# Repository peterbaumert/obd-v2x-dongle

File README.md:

# obd-v2x-dongle

Hobby OBD-II plug-in dongle that reads vehicle data, receives ITS-G5 (802.11p) V2X messages and uploads everything over LTE.

> **Receive-only for ITS-G5.** Transmitting on the 5.9 GHz ITS band requires EN 302 571 compliant equipment (or an experimental licence from the Bundesnetzagentur). This project does not transmit V2X messages.

## Status

**Rev 2 is ordered** (2026-11-26, PCBWay, assembled; boards expected around the turn of the year). Nothing has been
built yet: rev 1 was cancelled before production in favour of rev 2, so the first rev 2 boards are also the first
test of the circuit and the firmware. Details: [`rev2/README.md`](rev2/README.md); order, parts and cost:
[`rev2/docs/bom-notes.md`](rev2/docs/bom-notes.md).

## Architecture

```
OBD-II J1962 plug
 ├─ pin 16 (+12 V) ──► reverse-polarity + TVS (ISO 7637 / 16750) ──► 3 A buck ──► 3.8 V (LTE)  ──► 3.3 V LDO (logic)
 ├─ pin 6/14 (CAN) ──► CAN transceiver ──► ESP32-C5 TWAI
 ├─ pin 7 (K-Line) ──► K-Line transceiver ──► ESP32-C5 UART
 └─ pin 4/5 (GND)

ESP32-C5-WROOM-1U ── u.FL ──► 5.9 GHz antenna   (ITS-G5 RX via esphome-its-g5, BLE for setup)
        │ UART
Quectel EC200U-EU (LTE Cat 1 + GNSS) ── LTE antenna (U.FL), GNSS patch with SAW + LNA front end, micro-SIM
1S LiPo backup cell with charger and power mux
```

### Power management
- Ignition detection (supply > ~13.2 V or CAN activity) to sleep the modem when parked
- Low-battery cutoff (~11.8 V) to avoid draining the car battery
- Cranking ride-through down to ~6 V

## Rev 2 (current)

Two stacked 45 × 45 mm boards (4 layers each, joined by 2 × 8 headers and two spacers) in a 3D-printed case of
**68.1 × 49.6 × 26.4 mm including the plug**. The carrier holds the plug, power and the LTE modem; the upper board the
ESP32-C5, the transceivers, the SIM, the charger and the GNSS patch.

| Carrier (plug, power, LTE modem underneath) | Upper board (ESP32-C5, transceivers, SIM, GNSS patch on top) |
|---|---|
|  |  |
|  |  |

Renders from KiCad (`rev2/hardware/tools/render.py`); the LTE modem and the GNSS patch have no 3D model, so only
their pads show.

## Repo layout

| Path | Contents |
|---|---|
| `rev2/` | Rev 2, ordered: `hardware/` (two KiCad 10 projects, the assembly panel, tools), `mechanical/` (stack model, case), `docs/` (BOMs, order notes) |
| `rev1/` | Rev 1, a single 52 × 64.4 mm board: fully designed and routed, cancelled before production. Kept as the reference circuit and for its bring-up procedure |
| `firmware/` | ESP32-C5 firmware (ESPHome), shared by both revisions |

## Related

- [esphome-its-g5](https://github.com/peterbaumert/esphome-its-g5) — ESP32-C5 ITS-G5 receiver component

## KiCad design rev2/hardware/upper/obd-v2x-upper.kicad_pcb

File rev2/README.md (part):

# Rev 2: two stacked boards in a 25 mm case

Status: **both boards placed and routed after a layout review (2026-11-21): nothing unconnected, no rule errors,
schematic parity 0; stack model and case check pass; case fit tests printed (2026-11-22).** Order files, stock
check and order notes are ready (2026-11-24, [`docs/bom-notes.md`](docs/bom-notes.md)). **Ordered from PCBWay on
2026-11-26** (one panel, 5 bare + 2 assembled, i.e. two dongles); PCBWay's engineering questions were answered on
2026-11-27 (mouse-bite spacing, and solder-mask openings on the through-hole pads that the panel file had lost, see
"Ordering"), so the boards are due around the turn of the year. The rev 1 order (`../rev1/`) was cancelled on
2026-11-24 in favour of rev 2, so the shared circuit has not been tested on a built board.
Rev 2 lives in this folder (`hardware/`, `mechanical/`, `docs/`). The firmware (`../firmware/`) is shared.

## Goal

Close to the size of a commercial OBD tracker (about 67 × 50 × 25 mm): **68.1 × 49.6 × 26.4 mm including the plug**, instead of rev 1's
87.4 × 56.6 × 34.1 mm. Same functions as rev 1 except for the changes under "Decisions".

## How it gets smaller

Rev 1 is one 52 × 64.4 mm board. The 18 mm above it (the height of the OBD plug) is mostly empty, and parts up to
10 mm tall hang below it. Rev 2 uses that space:

- **Same OBD plug** (CR-PG001, 90° through-hole), still entirely in front of the board edge.
- **Two boards of about 45 × 45 mm**, stacked, joined by board-to-board headers.
- **Carrier board** (lower): the plug, and the LTE module flat on the underside. Nothing else below the board is
  taller than the module (2.6 mm at most).
- **Upper board**: sits 12 mm above the carrier, inside the plug's own height.

### Height budget (z = 0 at the carrier's bottom face)

| From | To | What |
|---|---|---|
| −4.5 | −2.9 | floor, 1.6 mm |
| −2.9 | 0 | EC200U (2.4 ± 0.2 mm) + 0.3 mm clearance; the plug's leg tips reach −1.0 |
| 0 | 1.6 | carrier board |
| 1.6 | 13.6 | gap between the boards, 12.0 mm: carrier top-side parts, the backup cell, upper-board underside parts |
| 13.6 | 15.2 | upper board |
| 15.2 | 19.9 | GNSS patch (4.0 ± 0.4 mm) + clearance; the plug's key ends at 18.3 |
| 19.9 | 21.9 | roof, 2.0 mm, with a 1 mm pocket over the patch's feed-pin head |

Total **26.4 mm**.

- **The gap is 12.0 mm, set by M2.5 × 12 mm spacers** in the two front corners. The connectors must not bottom
  out first. A surface-mount header and socket stand on their leads and bottom out at 12.1 ± 0.4 mm, which would
  bow the boards. So the upper board carries a through-hole header (2.5 mm base, flat on the board) and the
  carrier a surface-mount socket (top 8.9 mm above its board): 11.4 mm, 11.8 at most, 0.6 mm short of bottoming.
  The header pins still reach 5.4 mm into the socket.
- **The plug sits as in rev 1**, 1.0 mm below the carrier's bottom face. Its legs end 1.0 mm under the upper
  board (drawing: upper leg row 13.2 mm above the housing bottom, legs 0.8 mm thick).

### Footprint

- Width: 45 mm board + 2 × 0.3 mm gap + 2 × 2 mm wall = **49.6 mm**.
- Length: 2 mm rear wall + 0.3 mm gap + 45 mm board + 0.35 mm + 20 mm plug = **67.7 mm**. The case front ends at the
  plug's retention groove, as in rev 1.

### Does it fit? (part areas from the rev 1 board)

One side of a 45 × 45 mm board is 2025 mm². Rev 1 uses 1272 mm² of parts on top and 1047 mm² below, on 3349 mm².

| Part | Size | Height | Goes on |
|---|---|---|---|
| EC200U-EU | 28 × 31 mm | 2.4 ± 0.2 mm | carrier, underside |
| ESP32-C5-WROOM-1U | 18 × 21 mm | 3.4 mm | upper board, underside |
| Micro-SIM holder | about 16 × 15 mm | 1.45 mm | upper board, underside, at the left edge (slot in the case) |
| Buck inductor | 7 × 7 mm | 4.8 mm | carrier, top side |
| 220 µF tantalums | 7 × 4 mm | 3.1 mm | carrier, top side |
| USB-C | 9 × 8 mm | 3.3 mm | upper board, rear edge |
| Plug legs | 32 × 7 mm | through-hole | carrier, front edge, blocks both sides |

## Board split

Decided by area: with everything except the ESP32 on the carrier, its free area would be about 65 % full and the
upper board's about 9 %. With the split below it is about 45 % and 26 % (courtyard areas from the rev 1 board).

**Carrier:** J201 with the bus protection at its pins (CAN TVS, K-line capacitor and TVS), input protection, buck,
3.3 V regulator, EC200U with its supply caps, level shifter, LTE U.FL, GNSS U.FL (jumper to the upper board), the
cell connector and the power mux. The mux and the cell connector sit here because the modem's supply current then
never has to cross the connectors. 73 parts.

**Upper board:** ESP32-C5 module, USB-C, LED, RESET / BOOT buttons, the CAN and K-line transceivers, the micro-SIM
holder with its resistors and capacitors, the cell charger with its NTC (only 70 mA of charge current crosses the
stack; the NTC sits over the cell), the VIN sense divider, the open-collector drivers for the modem's PWRKEY and
RESET_N, and the ceramic GNSS patch on the top side with its front end and a U.FL for the jumper. 65 parts.

The carrier is the crowded one (the modem takes most of its underside, the cell limits part height over half of
its top), so everything that does not have to be next to the plug, the modem or the supply path is upstairs.

**Across the connectors** (two 2 × 8, 32 pins): 18 lines, 3 × 3.3 V, 1 × VSYS 3.8 V and 10 × GND.

| Connector | Lines |
|---|---|
| left (J601 / J701): the plug's bus pins and the modem's UART side | CANH, CANL (a facing pin pair), K_LINE, VIN_PROT (vehicle voltage for the K-line pull-up), modem UART TX / RX / RTS / CTS, STATUS |
| right (J602 / J702): the modem's SIM and power-key side | PWRKEY and RESET_N (open-collector lines), LTE power enable, USB VBUS, SIM VDD / RST / CLK / DATA, VSYS 3.8 V, VCELL (charger to cell) |

The pin lists are `STACK_A` / `STACK_B` in `hardware/tools/gen_schematic.py`.

## Schematics

Two KiCad 10 projects, generated like rev 1's (edit `hardware/tools/gen_schematic.py`, then run it):

| Project | Sheets |
|---|---|
| `hardware/carrier/obd-v2x-carrier` | power, vehicle, lte, battery (cell connector, power mux), stack_carrier |
| `hardware/upper/obd-v2x-upper` | mcu, xcvr (transceivers), sim, gnss, charger, sense, keys, stack_upper |

```bash
python rev2/hardware/tools/gen_schematic.py     # writes both projects
python rev2/hardware/tools/check_stack.py       # same net on mating connector pins, nothing shared left uncrossed
python rev2/hardware/tools/check_vs_rev1.py     # both boards joined = rev 1's circuit, apart from the listed changes
kicad-cli sch erc rev2/hardware/carrier/obd-v2x-carrier.kicad_sch
kicad-cli sch erc rev2/hardware/upper/obd-v2x-upper.kicad_sch
```

State: ERC 0 violations on both boards, `check_stack.py` passes (21 nets cross), and `check_vs_rev1.py` confirms
that the two boards joined through the connectors are connected exactly like rev 1's reviewed netlist, apart from
the intended changes. The circuits are rev 1's with
these changes: eSIM and SIM switch removed (IO12 is a spare test pad), micro-SIM holder, side-entry battery
connector, the two board-to-board connectors with spacer holes, and the GNSS patch with its front end.

GNSS on the upper board (sheet `gnss`): patch -> SKY65943-11 -> 33 pF DC block -> U.FL J801, joined by a jumper
cable to the carrier's GNSS socket J403. The front end is powered on the upper board, from the MCU pin that
switches the modem on (LTE_PWR_EN, 3 mA) through 100 Ω and 100 nF: about 3.0 V, under the part's 3.3 V limit, and
only while the modem is on. Its enable pin is tied to that supply. So the coax carries no DC and rev 1's antenna
bias switch (U405 with L401, C418, C419, C420, R415) is gone. R802 (not fitted) is a bypass link for trying the
bare patch.

New footprints, each drawn from the manufacturer's drawing (sources in `hardware/lib/gen_footprints.py`):
Molex 78646-3001 micro-SIM holder, Skyworks SKY65943-11, Taoglas CGGBP.25.4.A.02 patch.

Not done yet:

- **Footprint review against real parts:** the three new footprints come from the drawings and have not been
  checked on paper prints or parts (PCBWay's review saw them before assembly). The SKY65943-11's ground pad sizes
  and the patch's feed pad (1.4 mm on top, 2.2 mm on the bottom) are my choices.
- **GNSS details to confirm:** whether the SKY65943-11's RF pins carry DC (the data sheet does not say; a DC
  block sits on its output for that reason), and ESD protection at the patch (the part is rated only 250 V HBM).

## Boards

`<KiCad>/bin/python rev2/hardware/tools/gen_pcb.py carrier|upper` builds each board from its schematic: 45 × 45 mm
outline, rules, all footprints with their nets, ground pours. `--force` regenerates a board and loses any routing.

| Board | Layers | Why |
|---|---|---|
| carrier | 4 | The modem has pads under its body and the LTE antenna line needs a ground layer right below it |
| upper | 4 | F.Cu under the GNSS patch has to stay solid ground (the patch's ground plane); with that, two layers left no room for the SIM lines and the rest. In1 GND plane, In2 routing |

No paid impedance control: the antenna lines are designed to the fab's standard stack-up. ENIG on both boards (they
are ordered as one panel; flat pads for the modem and the QFNs).

Placement:

- **The parts that define the stack are placed as in the stack model:** plug, connectors, spacer holes, modem,
  ESP32 module, USB-C, micro-SIM holder, GNSS patch and front end, and the carrier's tall parts (battery connector,
  inductor, tantalums) in its front half.
- **Every other part is placed automatically** next to a part it shares a net with, and only where it fits by
  height: at most 2.9 mm under the cell, 2.65 mm on the carrier's underside, 0.7 mm on the upper board's underside
  over the plug legs. The heights are a table in `gen_pcb.py` (by footprint): data-sheet maxima for the tall parts,
  typical values for the rest. That was the starting point; the layout review and routing below moved many parts
  by hand.
- **Antenna sockets:** LTE and GNSS U.FL in the carrier's rear right corner, beside the cell.
- **The lid side of the upper board carries what must be reached or seen:** the two buttons and the LED.
  The case lid has pin holes and a 3 mm hole for a light rod there.
- **Changes the placement forced:** the connectors sit 0.6 mm inside the board edges (their SMD pads need 8.2 mm);
  the buck regulator uses the footprint without thermal vias, because the modem's pads are on the other side; the
  input TVS is on the carrier's underside beside the modem; the patch sits 1.5 mm left of centre so the USB-C
  socket's legs are not under it.

- **Modem orientation:** antenna pins at the rear, next to the LTE and GNSS sockets in the rear corners; UART,
  status and supply pins on its left side, where a strip of the underside stays free (level shifter, input TVS);
  SIM and power-key pins at the front and right. The connector pins are assigned to match.

### Routing

```bash
FREEROUTING_JAR=<freerouting-2.x.jar> <KiCad>/bin/python rev2/hardware/tools/autoroute.py upper   # Freerouting, Java 25
<KiCad>/bin/python rev2/hardware/tools/stitch.py upper        # GND vias where the two pours overlap
<KiCad>/bin/python rev2/hardware/tools/route_unconnected.py carrier|upper   # single connections with maze.py
```

- **Both boards are routed.** DRC on each: 0 unconnected, schematic parity 0, no rule errors. What remains is
  part outlines from the libraries touching neighbouring pads (the fab clips silkscreen off pads) and the USB-C outline
  at the rear edge, which the connector overhangs on purpose.
- **Upper board:** placed, then routed from scratch on 4 layers with `autoroute.py`; `finish.py`, `stitch.py`,
  `islands.py`, `padvia.py`; a few connections by hand. No signal copper on F.Cu under the patch.
- **Carrier:** the buck and the modem supply were re-placed at their pins (see "Layout review"), the nets around
  them ripped up and routed again with Freerouting (the rest locked), the last connections by hand in KiCad / the
  KiCad MCP: VBUCK into the power mux over In2, the compensation / feedback column re-ordered (COMP on F.Cu beside it,
  FB over In2, their ground to U102's exposed pad), the UART lines and K-line re-routed around them.
- **From here on the two `.kicad_pcb` files are the source.** `gen_pcb.py --force` rebuilds the placement but
  loses the routing and the hand edits; `PLACE` in `gen_pcb.py` records the positions of the parts it lists.
- **Rules:** Switch class (buck switch node) 0.8 mm, Modem class (VBAT_LTE) 0.6 mm, other supplies 0.4 mm on the
  carrier; vehicle-voltage nets keep 0.2 mm clearance; one thermal-relief spoke is enough. `widen.py` then widened
  every supply segment that had room: the switch node is 10 mm of 0.8-1.0 mm track on F.Cu without vias, VBAT_LTE
  mostly 1.0 mm. RF lines are 0.32 mm throughout (0.27 mm only into the front end's own pads); the LTE line runs
  27 mm from the corner U.FL (about 0.2-0.3 dB).
- **Under the carrier's top parts is the modem:** its edge pads (2.5 mm long, 0.5 mm apart) leave no room for a via
  beside them, and its centre GND pads only leave a few gaps. Check the underside before placing a via there.
- **Checked 2026-11-21:** buck loop by eye (C102 over VIN, D103's cathode under SW, L101 beside U102), switch node,
  supply widths, RF widths. Silkscreen: references placed beside their parts; about 30 per board have no free spot
  and are hidden (the CPL file carries the positions). Not checkable here: the patch on the 45 mm board (measure).

| Carrier, top | Carrier, underside | Upper, top | Upper, underside |
|---|---|---|---|
|  |  |  |  |

| Tool | What it does |
|---|---|
| `autoroute.py` | Freerouting on a DSN export (carrier: In1 declared a GND plane) |
| `route_unconnected.py`, `maze.py` | single connections, from rev 1 |
| `repair.py` | fixes via drills and thin tracks; rips up and re-routes every signal net in a rule error |
| `finish.py` | routes what is still open, GND pads included, with narrower tracks |
| `stitch.py` | GND vias where the pours of all layers overlap |
| `islands.py` | a via for each pour fragment that has none |
| `movepart.py` | moves a two-pad part next to the pin it belongs to and reconnects it |
| `localfix.py` | blunt local rip-up around a blocked pin; made things worse when tried, kept for reference |
| `padvia.py` | a GND via for a floating GND pad (rips signal nets in the way; run `finish.py` after) |
| `swapfp.py` | replaces placed footprints with the library version, or with another footprint (`REF=Lib:Name`) |
| `silk.py` | puts each reference beside its part where it is clear of pads and other silkscreen, or hides it |
| `widen.py` | widens supply tracks (and necked-down RF lines back to 0.32 mm) wherever the clearance allows |
| `fab.py` | order files per board: Gerber zip, assembly BOM, pick-and-place file; full BOMs to `docs/` |
| `check_stock.py` | LCSC stock of every part with an MPN, from the BOMs that `fab.py` writes |
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
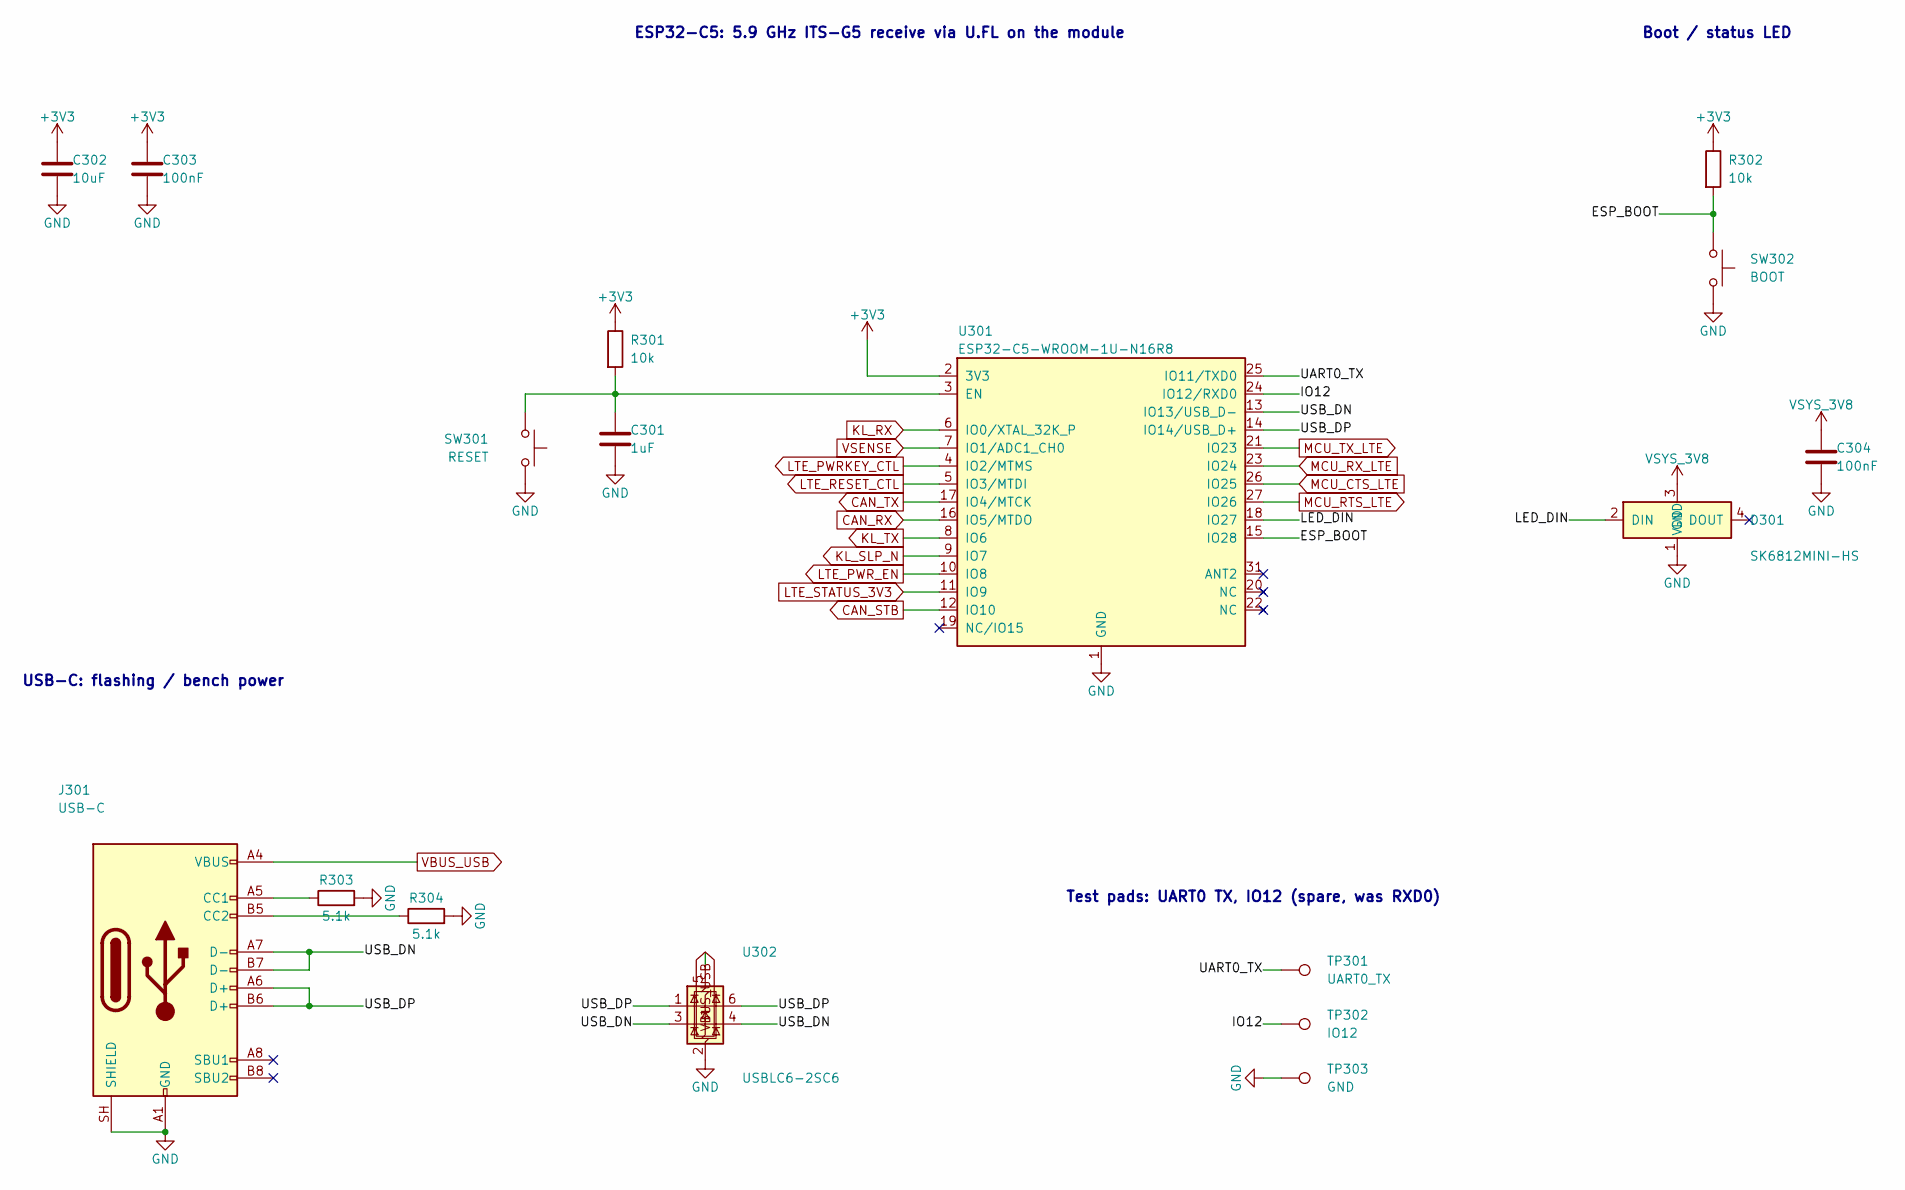
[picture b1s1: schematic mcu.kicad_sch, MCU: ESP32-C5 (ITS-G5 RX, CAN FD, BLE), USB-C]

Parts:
C301: 1uF; C_0603_1608Metric
C302: 10uF; C_0805_2012Metric
C303, C304: 100nF; C_0603_1608Metric
D301: SK6812MINI-HS; LED_SK6812MINI-HS_3.7x3.5mm; MPN SK6812MINI-HS; LCSC C2922787
J301: USB-C; USB_C_Receptacle_HRO_TYPE-C-31-M-12; MPN TYPE-C-31-M-12; LCSC C165948
R301, R302: 10k; R_0603_1608Metric
R303, R304: 5.1k; R_0603_1608Metric
SW301: RESET; SW_SPST_TL3342; MPN TL3342F450QG; LCSC C2886897
SW302: BOOT; SW_SPST_TL3342; MPN TL3342F450QG; LCSC C2886897
TP301: UART0_TX; TestPoint_Pad_D1.0mm
TP302: IO12; TestPoint_Pad_D1.0mm
TP303: GND; TestPoint_Pad_D1.0mm
U301: ESP32-C5-WROOM-1U-N16R8; ESP32-C5-WROOM-1U; MPN ESP32-C5-WROOM-1U-N16R8-V1.2; LCSC C54951857
U302: USBLC6-2SC6; SOT-23-6; MPN USBLC6-2SC6; LCSC C2827654

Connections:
/MCU (ESP32-C5, USB)/ESP_BOOT: R302.2, SW302.1, U301.15 (IO28)
/MCU (ESP32-C5, USB)/IO12: TP302.1, U301.24 (IO12/RXD0)
/MCU (ESP32-C5, USB)/LED_DIN: D301.2 (DIN), U301.18 (IO27)
/MCU (ESP32-C5, USB)/UART0_TX: TP301.1, U301.25 (IO11/TXD0)
/MCU (ESP32-C5, USB)/USB_DN: J301.A7 (D-), J301.B7 (D-), U301.13 (IO13/USB_D-), U302.3 (I/O2), U302.4 (I/O2)
/MCU (ESP32-C5, USB)/USB_DP: J301.A6 (D+), J301.B6 (D+), U301.14 (IO14/USB_D+), U302.1 (I/O1), U302.6 (I/O1)
CAN_RX: U301.16 (IO5/MTDO); also elsewhere on the board
CAN_STB: U301.12 (IO10); also elsewhere on the board
CAN_TX: U301.17 (IO4/MTCK); also elsewhere on the board
KL_RX: U301.6 (IO0/XTAL_32K_P); also elsewhere on the board
KL_SLP_N: U301.9 (IO7); also elsewhere on the board
KL_TX: U301.8 (IO6); also elsewhere on the board
LTE_PWRKEY_CTL: U301.4 (IO2/MTMS); also elsewhere on the board
LTE_PWR_EN: U301.10 (IO8); also elsewhere on the board
LTE_RESET_CTL: U301.5 (IO3/MTDI); also elsewhere on the board
LTE_STATUS_3V3: U301.11 (IO9); also elsewhere on the board
MCU_CTS_LTE: U301.26 (IO25); also elsewhere on the board
MCU_RTS_LTE: U301.27 (IO26); also elsewhere on the board
MCU_RX_LTE: U301.23 (IO24); also elsewhere on the board
MCU_TX_LTE: U301.21 (IO23); also elsewhere on the board
unnamed: J301.A5 (CC1), R303.1
unnamed: J301.B5 (CC2), R304.1
unnamed: C301.1, R301.2, SW301.1, U301.3 (EN)
VBUS_USB: J301.A4 (VBUS), J301.A9 (VBUS), J301.B4 (VBUS), J301.B9 (VBUS), U302.5 (VBUS); also elsewhere on the board
VSENSE: U301.7 (IO1/ADC1_CH0); also elsewhere on the board

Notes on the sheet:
Test pads: UART0 TX, IO12 (spare, was RXD0)
USB-C: flashing / bench power
ESP32-C5: 5.9 GHz ITS-G5 receive via U.FL on the module
Boot / status LED

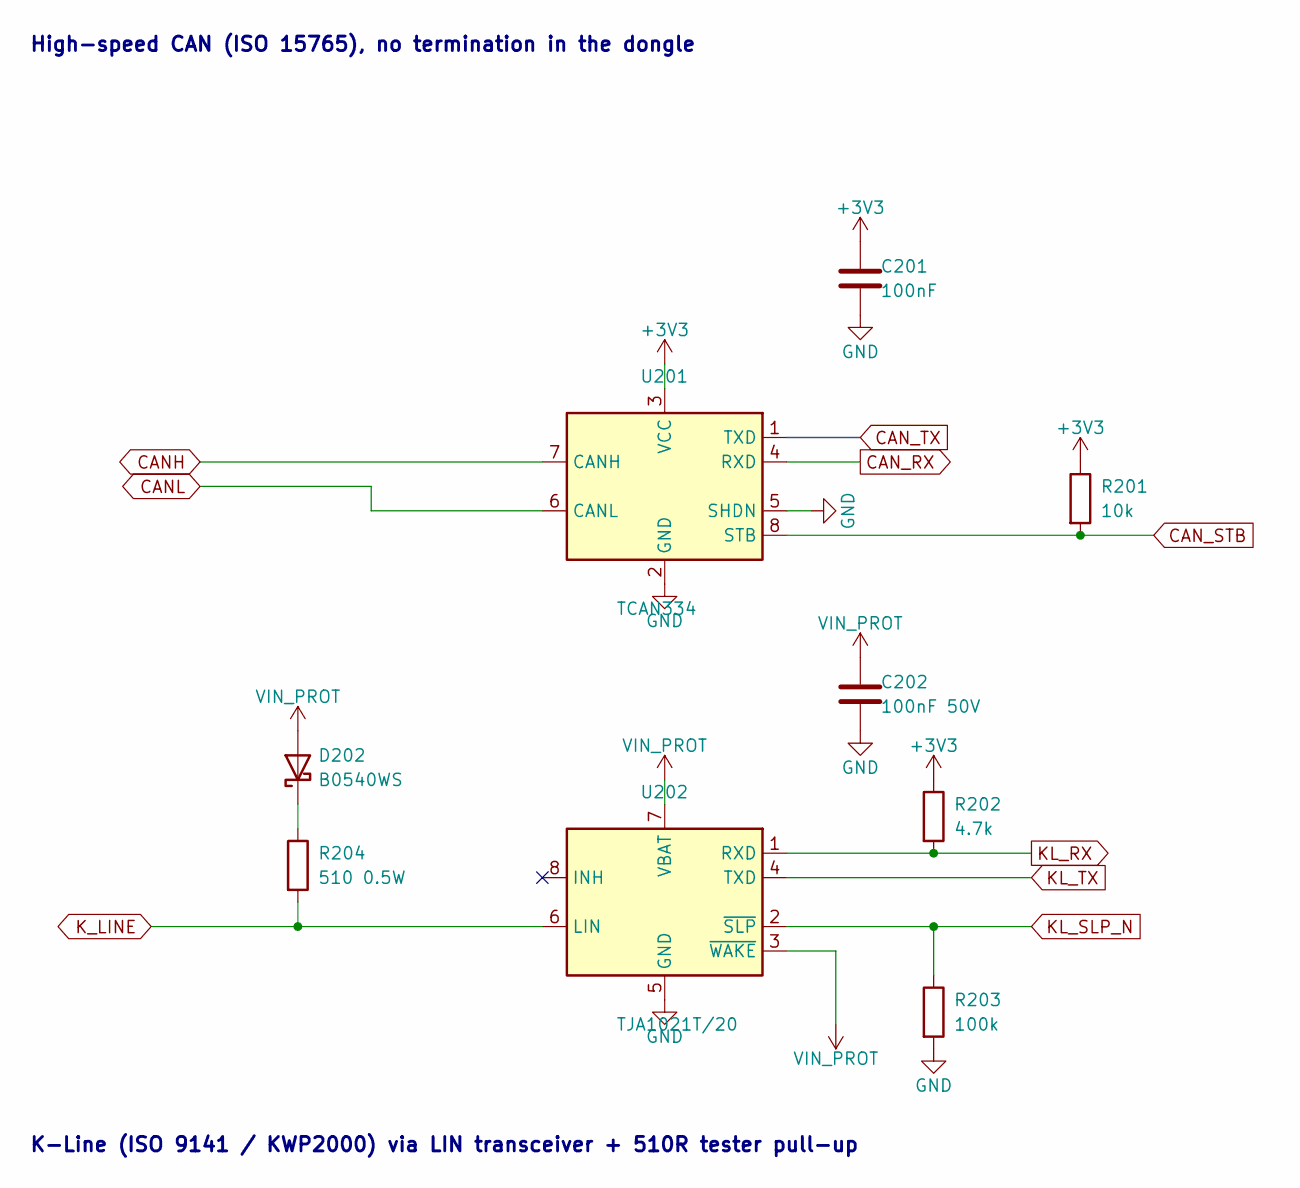
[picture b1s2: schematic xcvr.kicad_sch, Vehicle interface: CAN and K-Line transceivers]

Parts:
C201: 100nF; C_0603_1608Metric
C202: 100nF 50V; C_0603_1608Metric
D202: B0540WS; D_SOD-323; MPN B0540WS-7; LCSC C52754523
R201: 10k; R_0603_1608Metric
R202: 4.7k; R_0603_1608Metric
R203: 100k; R_0603_1608Metric
R204: 510 0.5W; R_1206_3216Metric
U201: TCAN334; SOIC-8_3.9x4.9mm_P1.27mm; MPN TCAN334DR; LCSC C2871143
U202: TJA1021T/20; SOIC-8_3.9x4.9mm_P1.27mm; MPN TJA1021T/20/CM,118; LCSC C128810

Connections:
CANH: U201.7 (CANH); also elsewhere on the board
CANL: U201.6 (CANL); also elsewhere on the board
CAN_RX: U201.4 (RXD); also elsewhere on the board
CAN_STB: R201.2, U201.8 (STB); also elsewhere on the board
CAN_TX: U201.1 (TXD); also elsewhere on the board
KL_RX: R202.2, U202.1 (RXD); also elsewhere on the board
KL_SLP_N: R203.1, U202.2 (~SLP); also elsewhere on the board
KL_TX: U202.4 (TXD); also elsewhere on the board
K_LINE: R204.2, U202.6 (LIN); also elsewhere on the board
unnamed: D202.1 (K), R204.1

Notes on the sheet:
High-speed CAN (ISO 15765), no termination in the dongle
K-Line (ISO 9141 / KWP2000) via LIN transceiver + 510R tester pull-up

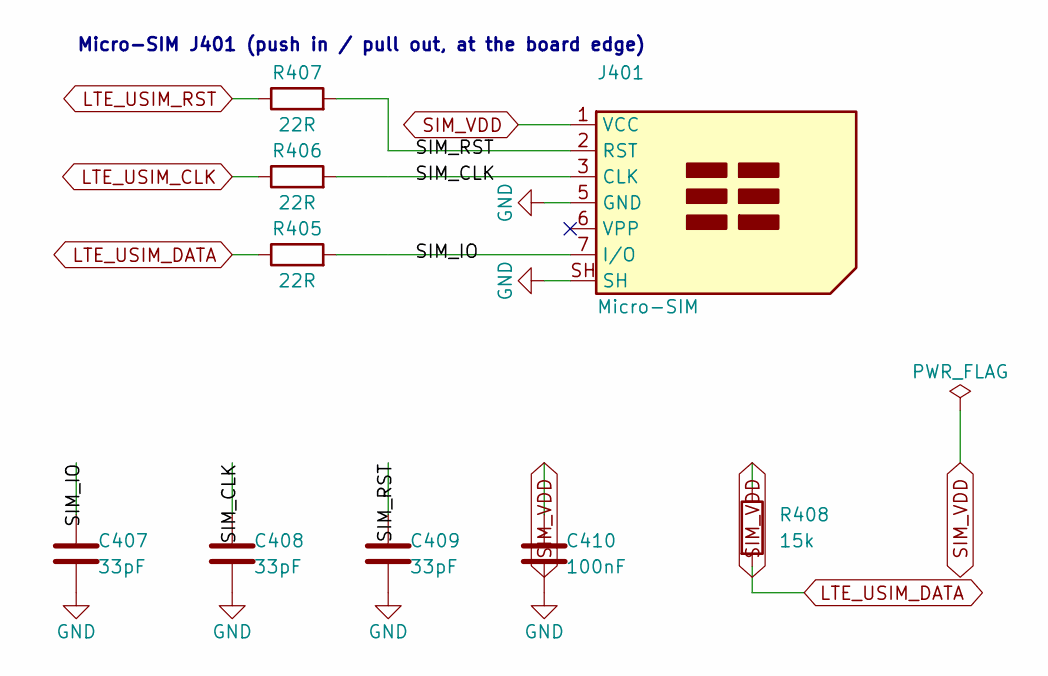
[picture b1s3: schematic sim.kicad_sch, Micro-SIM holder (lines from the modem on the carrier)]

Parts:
C407, C408, C409: 33pF; C_0402_1005Metric
C410: 100nF; C_0402_1005Metric
J401: Micro-SIM; microSIM_Molex_78646-3001; MPN 0786463001
R405, R406, R407: 22R; R_0402_1005Metric
R408: 15k; R_0402_1005Metric

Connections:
/Micro-SIM/SIM_CLK: C408.1, J401.3 (CLK), R406.2
/Micro-SIM/SIM_IO: C407.1, J401.7 (I/O), R405.2
/Micro-SIM/SIM_RST: C409.1, J401.2 (RST), R407.2
LTE_USIM_CLK: R406.1; also elsewhere on the board
LTE_USIM_DATA: R405.1, R408.2; also elsewhere on the board
LTE_USIM_RST: R407.1; also elsewhere on the board
SIM_VDD: C410.1, J401.1 (VCC), R408.1; also elsewhere on the board

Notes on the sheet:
Micro-SIM J401 (push in / pull out, at the board edge)

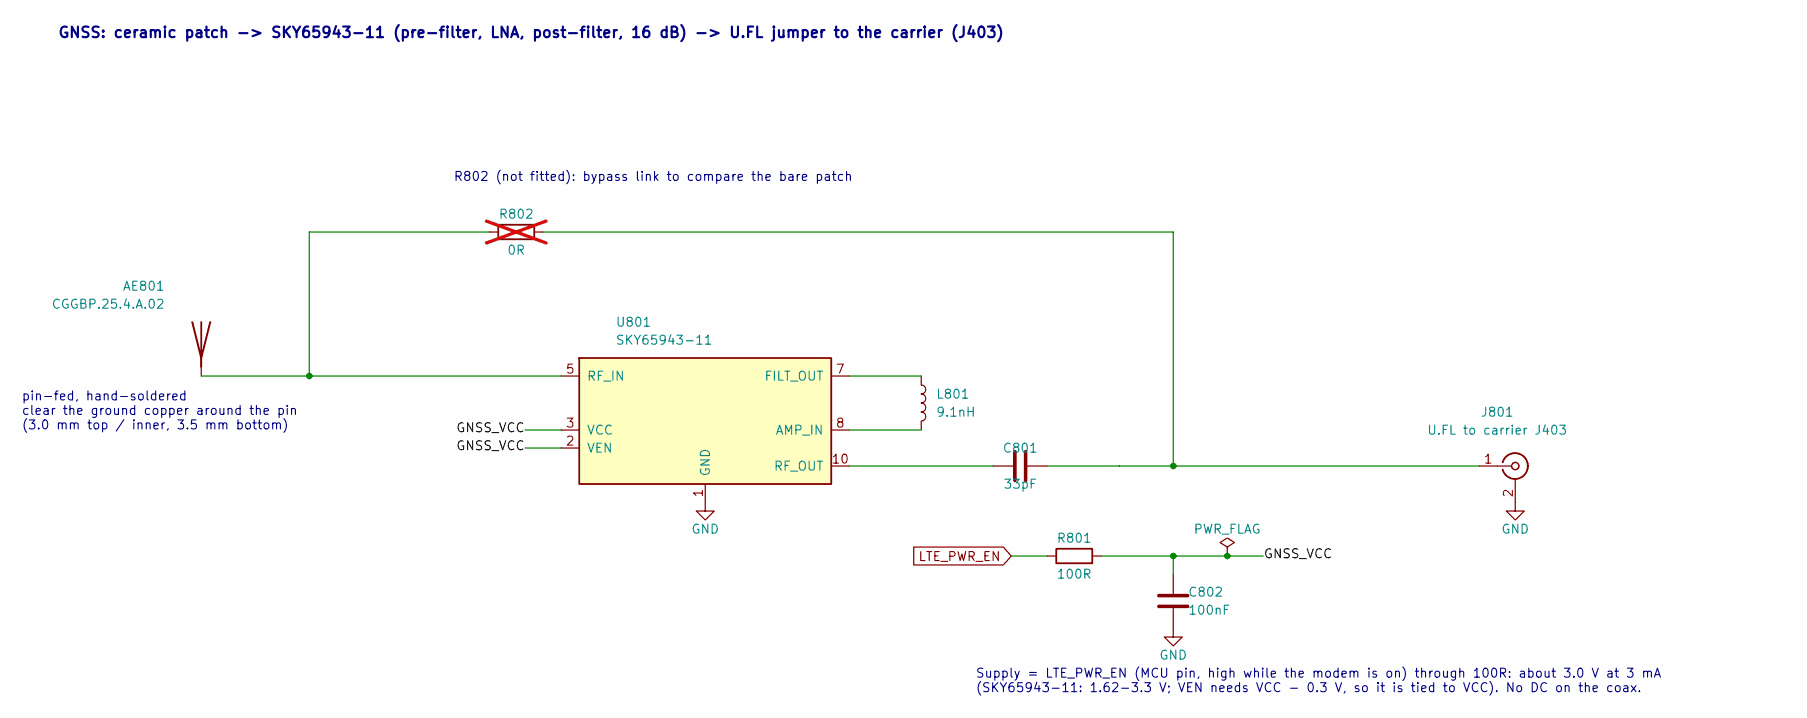
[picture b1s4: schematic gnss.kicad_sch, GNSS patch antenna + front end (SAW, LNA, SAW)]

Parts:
AE801: CGGBP.25.4.A.02; Antenna_Taoglas_CGGBP.25.4.A.02; MPN CGGBP.25.4.A.02
C801: 33pF; C_0402_1005Metric; MPN 0402CG330J500NT; LCSC C1562
C802: 100nF; C_0402_1005Metric
J801: U.FL to carrier J403; U.FL_Hirose_U.FL-R-SMT-1_Vertical; MPN U.FL-R-SMT-1(10); LCSC C88373
L801: 9.1nH; L_0402_1005Metric; MPN LQW15AN9N1J00D; LCSC C437364
R801: 100R; R_0402_1005Metric
R802: 0R; R_0402_1005Metric; not fitted
U801: SKY65943-11; Skyworks_SKY65943-11_MCM-10_2.5x2.5mm; MPN SKY65943-11; LCSC C2654442

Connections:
/GNSS patch + front end/GNSS_VCC: C802.1, R801.2, U801.2 (VEN), U801.3 (VCC)
LTE_PWR_EN: R801.1; also elsewhere on the board
unnamed: AE801.1, R802.1, U801.5 (RF_IN)
unnamed: C801.2, J801.1 (In), R802.2
unnamed: L801.2, U801.8 (AMP_IN)
unnamed: L801.1, U801.7 (FILT_OUT)
unnamed: C801.1, U801.10 (RF_OUT)

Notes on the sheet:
R802 (not fitted): bypass link to compare the bare patch
GNSS: ceramic patch -> SKY65943-11 (pre-filter, LNA, post-filter, 16 dB) -> U.FL jumper to the carrier (J403)
Supply = LTE_PWR_EN (MCU pin, high while the modem is on) through 100R: about 3.0 V at 3 mA (SKY65943-11: 1.62-3.3 V; VEN needs VCC - 0.3 V, so it is tied to VCC). No DC on the coax.
pin-fed, hand-soldered clear the ground copper around the pin (3.0 mm top / inner, 3.5 mm bottom)

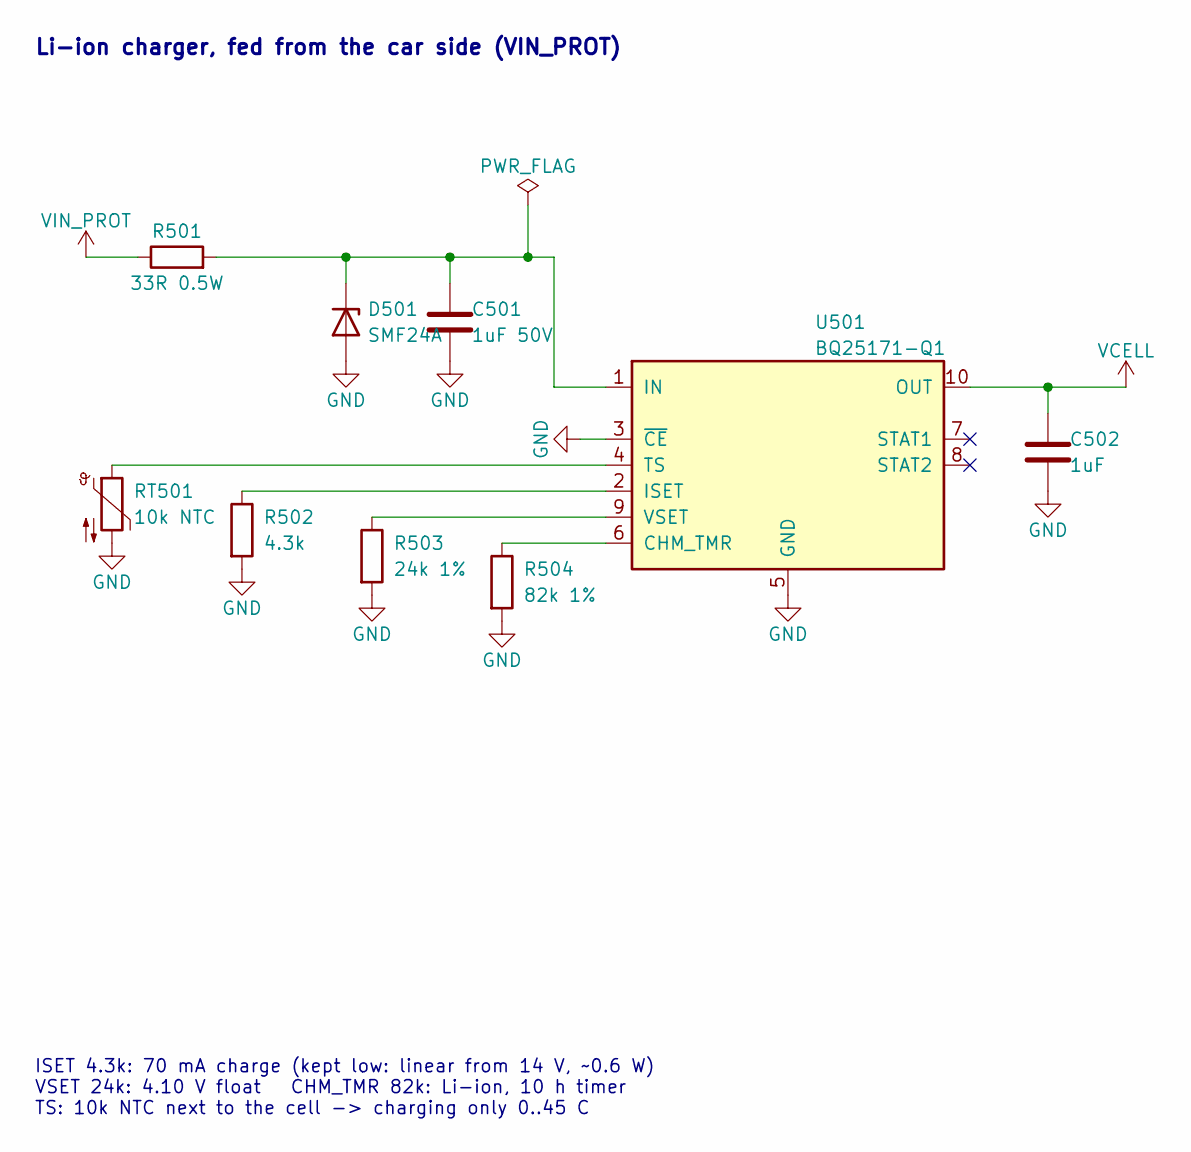
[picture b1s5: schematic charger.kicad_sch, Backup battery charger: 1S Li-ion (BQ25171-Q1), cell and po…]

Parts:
C501: 1uF 50V; C_0805_2012Metric
C502: 1uF; C_0603_1608Metric
D501: SMF24A; D_SOD-123F; MPN SMF24A; LCSC C315999
R501: 33R 0.5W; R_1206_3216Metric
R502: 4.3k; R_0603_1608Metric
R503: 24k 1%; R_0603_1608Metric
R504: 82k 1%; R_0603_1608Metric
RT501: 10k NTC; R_0603_1608Metric; MPN SDNT1608X103F3435FTF; LCSC C525660
U501: BQ25171-Q1; Texas_DRC0010J; MPN BQ25171QWDRCRQ1; LCSC C2861221

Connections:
unnamed: C501.1, D501.1 (K), R501.2, U501.1 (IN)
unnamed: R504.1, U501.6 (CHM_TMR)
unnamed: R502.1, U501.2 (ISET)
unnamed: RT501.1, U501.4 (TS)
unnamed: R503.1, U501.9 (VSET)
VCELL: C502.1, U501.10 (OUT); also elsewhere on the board

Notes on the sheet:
ISET 4.3k: 70 mA charge (kept low: linear from 14 V, ~0.6 W) VSET 24k: 4.10 V float CHM_TMR 82k: Li-ion, 10 h timer TS: 10k NTC next to the cell -> charging only 0..45 C
Li-ion charger, fed from the car side (VIN_PROT)

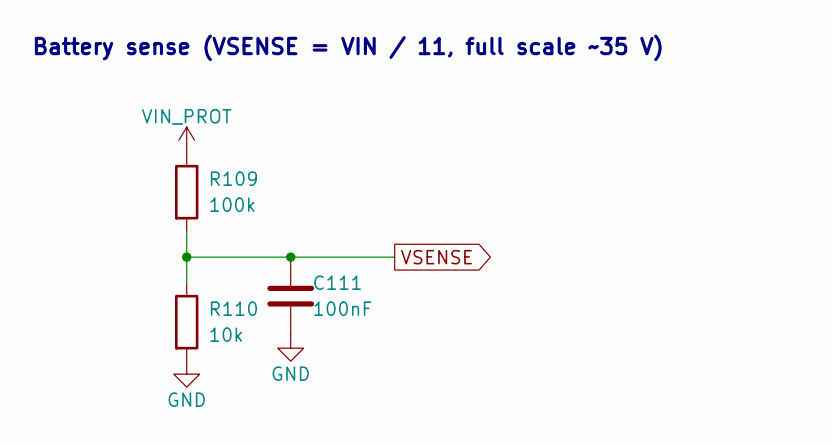
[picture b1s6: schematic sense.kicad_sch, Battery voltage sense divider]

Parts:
C111: 100nF; C_0603_1608Metric
R109: 100k; R_0603_1608Metric
R110: 10k; R_0603_1608Metric

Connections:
VSENSE: C111.1, R109.2, R110.1; also elsewhere on the board

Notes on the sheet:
Battery sense (VSENSE = VIN / 11, full scale ~35 V)

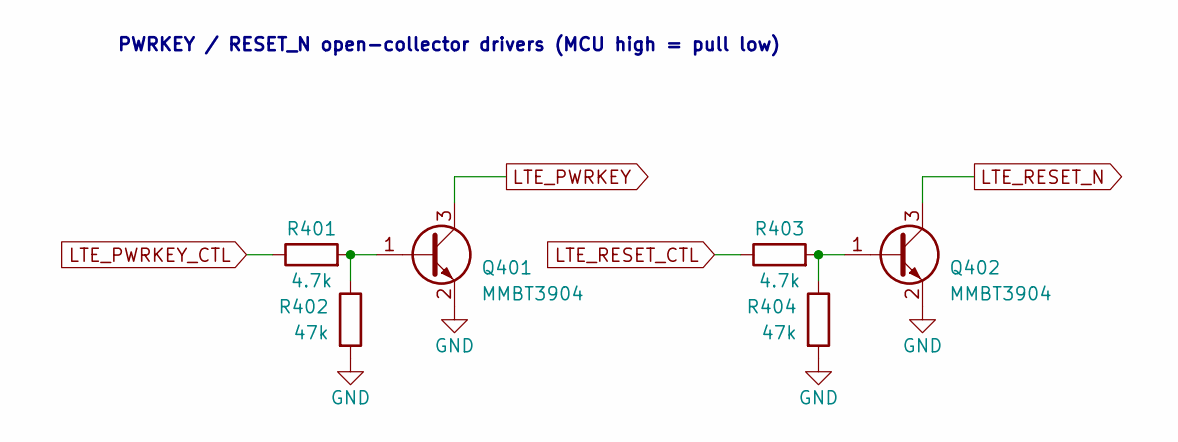
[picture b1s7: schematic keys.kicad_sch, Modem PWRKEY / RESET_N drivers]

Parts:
Q401, Q402: MMBT3904; SOT-23; MPN MMBT3904; LCSC C20526
R401, R403: 4.7k; R_0603_1608Metric
R402, R404: 47k; R_0603_1608Metric

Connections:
LTE_PWRKEY: Q401.3 (C); also elsewhere on the board
LTE_PWRKEY_CTL: R401.1; also elsewhere on the board
LTE_RESET_CTL: R403.1; also elsewhere on the board
LTE_RESET_N: Q402.3 (C); also elsewhere on the board
unnamed: Q401.1 (B), R401.2, R402.1
unnamed: Q402.1 (B), R403.2, R404.1

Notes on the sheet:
PWRKEY / RESET_N open-collector drivers (MCU high = pull low)

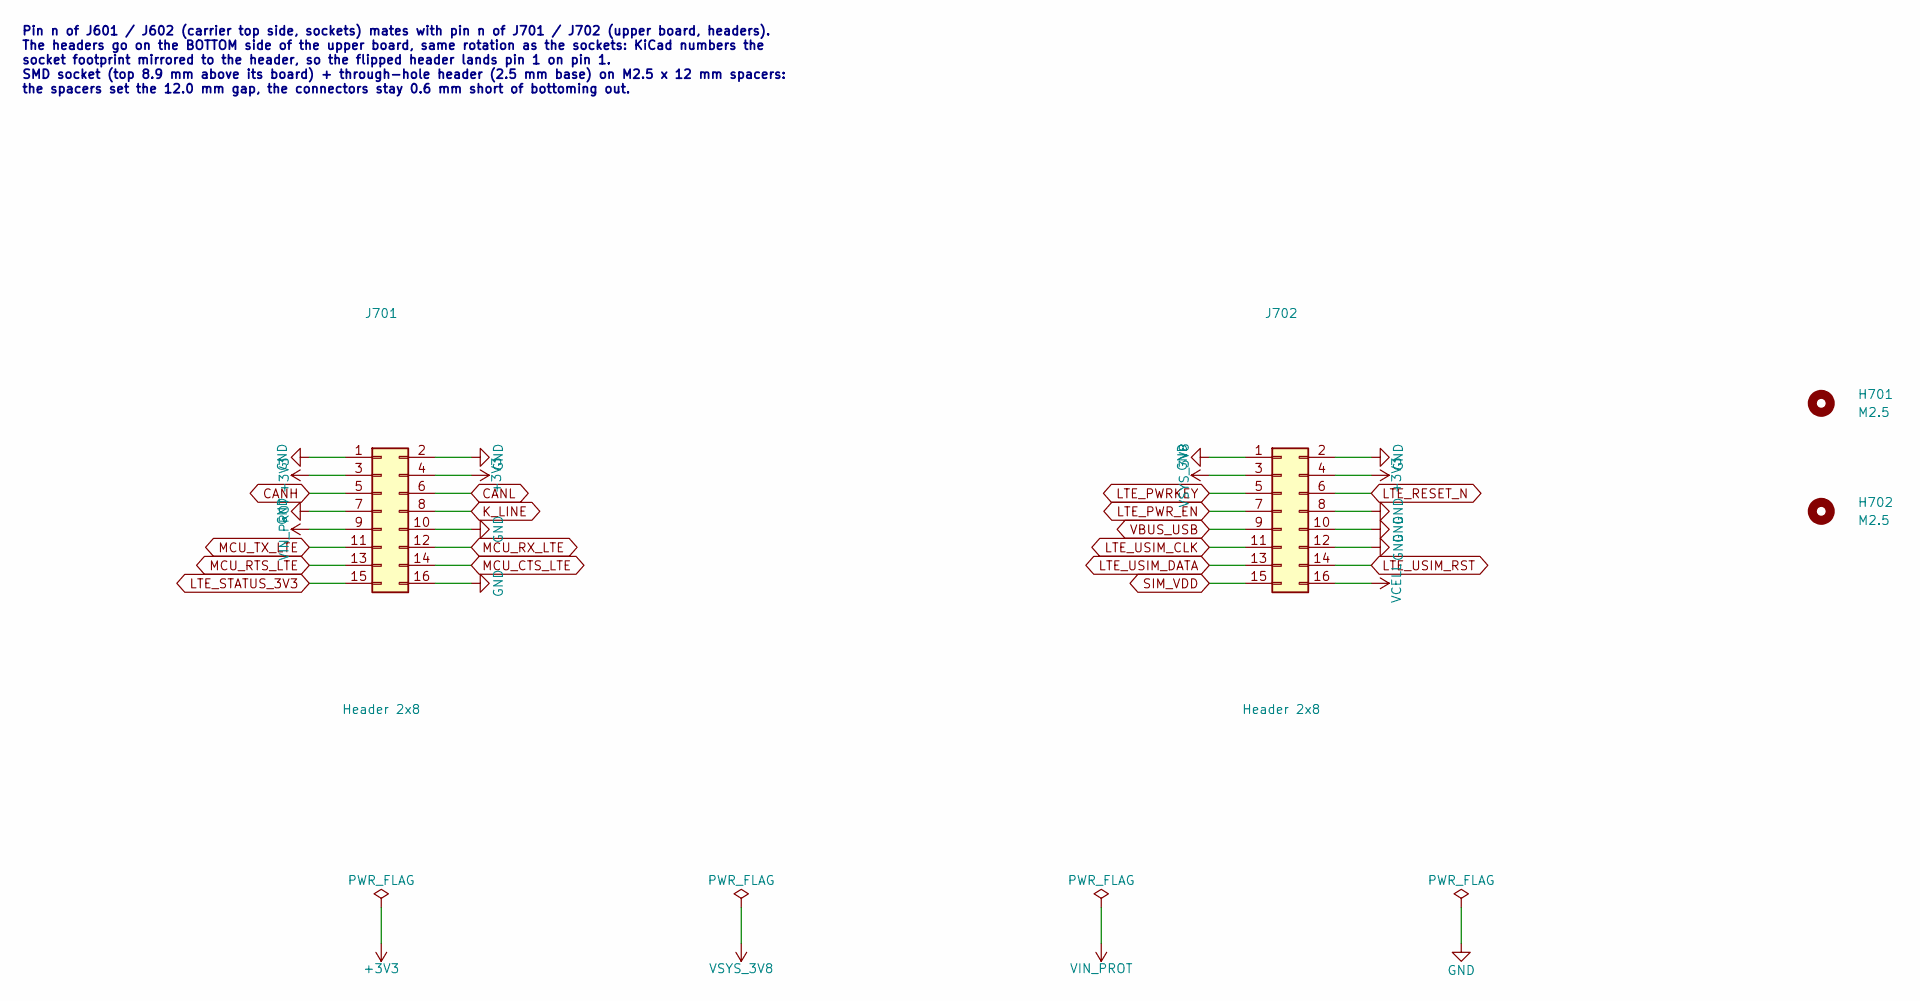
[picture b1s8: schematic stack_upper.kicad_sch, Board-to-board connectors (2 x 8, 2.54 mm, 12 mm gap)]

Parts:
H701, H702: M2.5; MountingHole_2.7mm_M2.5
J701, J702: Header 2x8; PinHeader_2x08_P2.54mm_Vertical; MPN HX PZ2.54-2x8P ZZ; LCSC C32713281

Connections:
CANH: J701.5; also elsewhere on the board
CANL: J701.6; also elsewhere on the board
K_LINE: J701.8; also elsewhere on the board
LTE_PWRKEY: J702.5; also elsewhere on the board
LTE_PWR_EN: J702.7; also elsewhere on the board
LTE_RESET_N: J702.6; also elsewhere on the board
LTE_STATUS_3V3: J701.15; also elsewhere on the board
LTE_USIM_CLK: J702.11; also elsewhere on the board
LTE_USIM_DATA: J702.13; also elsewhere on the board
LTE_USIM_RST: J702.14; also elsewhere on the board
MCU_CTS_LTE: J701.14; also elsewhere on the board
MCU_RTS_LTE: J701.13; also elsewhere on the board
MCU_RX_LTE: J701.12; also elsewhere on the board
MCU_TX_LTE: J701.11; also elsewhere on the board
SIM_VDD: J702.15; also elsewhere on the board
VBUS_USB: J702.9; also elsewhere on the board
VCELL: J702.16; also elsewhere on the board

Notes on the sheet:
Pin n of J601 / J602 (carrier top side, sockets) mates with pin n of J701 / J702 (upper board, headers). The headers go on the BOTTOM side of the upper board, same rotation as the sockets: KiCad numbers the socket footprint mirrored to the header, so the flipped header lands pin 1 on pin 1. SMD soc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

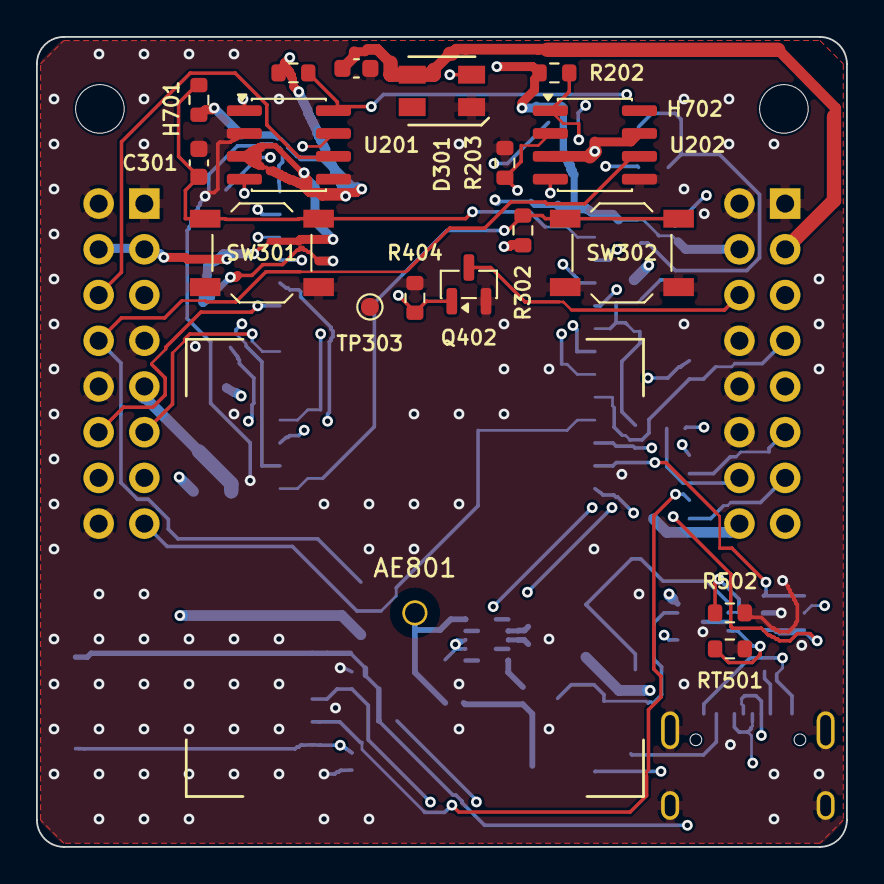
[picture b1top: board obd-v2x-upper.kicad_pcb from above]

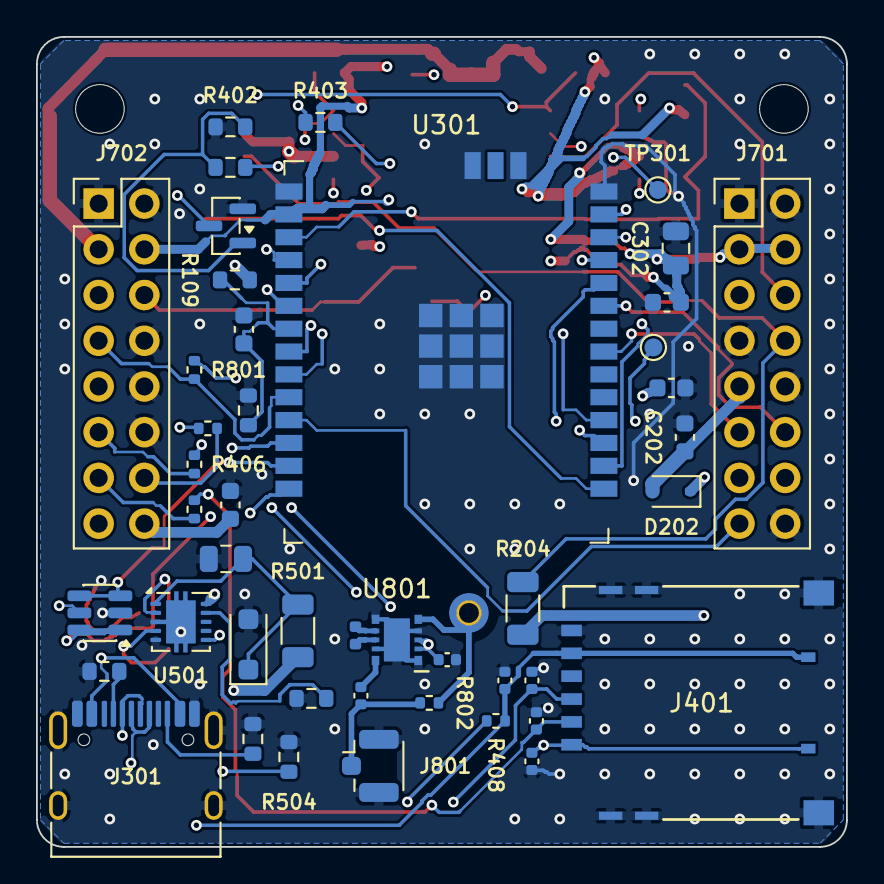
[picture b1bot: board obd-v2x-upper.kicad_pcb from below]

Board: 4 copper layers, 45.0 x 45.0 mm, 65 parts (45 on the bottom side), 56 nets.

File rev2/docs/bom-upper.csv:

"Reference","Value","Footprint","MPN","Manufacturer","LCSC","Qty","DNP"
"AE801","CGGBP.25.4.A.02","obd-v2x:Antenna_Taoglas_CGGBP.25.4.A.02","CGGBP.25.4.A.02","Taoglas","","1",""
"C111,C201,C303,C304","100nF","Capacitor_SMD:C_0603_1608Metric","","","","4",""
"C202","100nF 50V","Capacitor_SMD:C_0603_1608Metric","","","","1",""
"C301,C502","1uF","Capacitor_SMD:C_0603_1608Metric","","","","2",""
"C302","10uF","Capacitor_SMD:C_0805_2012Metric","","","","1",""
"C407,C408,C409","33pF","Capacitor_SMD:C_0402_1005Metric","","","","3",""
"C410,C802","100nF","Capacitor_SMD:C_0402_1005Metric","","","","2",""
"C501","1uF 50V","Capacitor_SMD:C_0805_2012Metric","","","","1",""
"C801","33pF","Capacitor_SMD:C_0402_1005Metric","0402CG330J500NT","FH","C1562","1",""
"D202","B0540WS","Diode_SMD:D_SOD-323","B0540WS-7","Diodes Inc","C52754523","1",""
"D301","SK6812MINI-HS","obd-v2x:LED_SK6812MINI-HS_3.7x3.5mm","SK6812MINI-HS","OPSCO","C2922787","1",""
"D501","SMF24A","Diode_SMD:D_SOD-123F","SMF24A","Littelfuse","C315999","1",""
"H701,H702","M2.5","MountingHole:MountingHole_2.7mm_M2.5","","","","2",""
"J301","USB-C","Connector_USB:USB_C_Receptacle_HRO_TYPE-C-31-M-12","TYPE-C-31-M-12","HRO","C165948","1",""
"J401","Micro-SIM","obd-v2x:microSIM_Molex_78646-3001","0786463001","Molex","","1",""
"J701,J702","Header 2x8","Connector_PinHeader_2.54mm:PinHeader_2x08_P2.54mm_Vertical","HX PZ2.54-2x8P ZZ","Hanxia","C32713281","2",""
"J801","U.FL to carrier J403","Connector_Coaxial:U.FL_Hirose_U.FL-R-SMT-1_Vertical","U.FL-R-SMT-1(10)","Hirose","C88373","1",""
"L801","9.1nH","Inductor_SMD:L_0402_1005Metric","LQW15AN9N1J00D","Murata","C437364","1",""
"Q401,Q402","MMBT3904","Package_TO_SOT_SMD:SOT-23","MMBT3904","onsemi","C20526","2",""
"R109,R203","100k","Resistor_SMD:R_0603_1608Metric","","","","2",""
"R110,R201,R301,R302","10k","Resistor_SMD:R_0603_1608Metric","","","","4",""
"R202,R401,R403","4.7k","Resistor_SMD:R_0603_1608Metric","","","","3",""
"R204","510 0.5W","Resistor_SMD:R_1206_3216Metric","","","","1",""
"R303,R304","5.1k","Resistor_SMD:R_0603_1608Metric","","","","2",""
"R402,R404","47k","Resistor_SMD:R_0603_1608Metric","","","","2",""
"R405,R406,R407","22R","Resistor_SMD:R_0402_1005Metric","","","","3",""
"R408","15k","Resistor_SMD:R_0402_1005Metric","","","","1",""
"R501","33R 0.5W","Resistor_SMD:R_1206_3216Metric","","","","1",""
"R502","4.3k","Resistor_SMD:R_0603_1608Metric","","","","1",""
"R503","24k 1%","Resistor_SMD:R_0603_1608Metric","","","","1",""
"R504","82k 1%","Resistor_SMD:R_0603_1608Metric","","","","1",""
"R801","100R","Resistor_SMD:R_0402_1005Metric","","","","1",""
"R802","0R","Resistor_SMD:R_0402_1005Metric","","","","1","DNP"
"RT501","10k NTC","Resistor_SMD:R_0603_1608Metric","SDNT1608X103F3435FTF","Sunlord","C525660","1",""
"SW301","RESET","Button_Switch_SMD:SW_SPST_TL3342","TL3342F450QG","E-Switch","C2886897","1",""
"SW302","BOOT","Button_Switch_SMD:SW_SPST_TL3342","TL3342F450QG","E-Switch","C2886897","1",""
"TP301","UART0_TX","TestPoint:TestPoint_Pad_D1.0mm","","","","1",""
"TP302","IO12","TestPoint:TestPoint_Pad_D1.0mm","","","","1",""
"TP303","GND","TestPoint:TestPoint_Pad_D1.0mm","","","","1",""
"U201","TCAN334","Package_SO:SOIC-8_3.9x4.9mm_P1.27mm","TCAN334DR","TI","C2871143","1",""
"U202","TJA1021T/20","Package_SO:SOIC-8_3.9x4.9mm_P1.27mm","TJA1021T/20/CM,118","NXP","C128810","1",""
"U301","ESP32-C5-WROOM-1U-N16R8","obd-v2x:ESP32-C5-WROOM-1U","ESP32-C5-WROOM-1U-N16R8-V1.2","Espressif","C54951857","1",""
"U302","USBLC6-2SC6","Package_TO_SOT_SMD:SOT-23-6","USBLC6-2SC6","ST","C2827654","1",""
"U501","BQ25171-Q1","Package_SON:Texas_DRC0010J","BQ25171QWDRCRQ1","Texas Instruments","C2861221","1",""
"U801","SKY65943-11","obd-v2x:Skyworks_SKY65943-11_MCM-10_2.5x2.5mm","SKY65943-11","Skyworks","C2654442","1",""
